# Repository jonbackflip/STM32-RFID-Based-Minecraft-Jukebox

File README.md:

# STM32-RFID-Based-Minecraft-Jukebox
An embedded music player based on the Minecraft Jukebox. Designed around an STM32F411CEU6, integrating RFID-based song selection, microSD storage, digital audio, user control via a rotary encoder with push-button, OLED display, and speaker/headphone output.

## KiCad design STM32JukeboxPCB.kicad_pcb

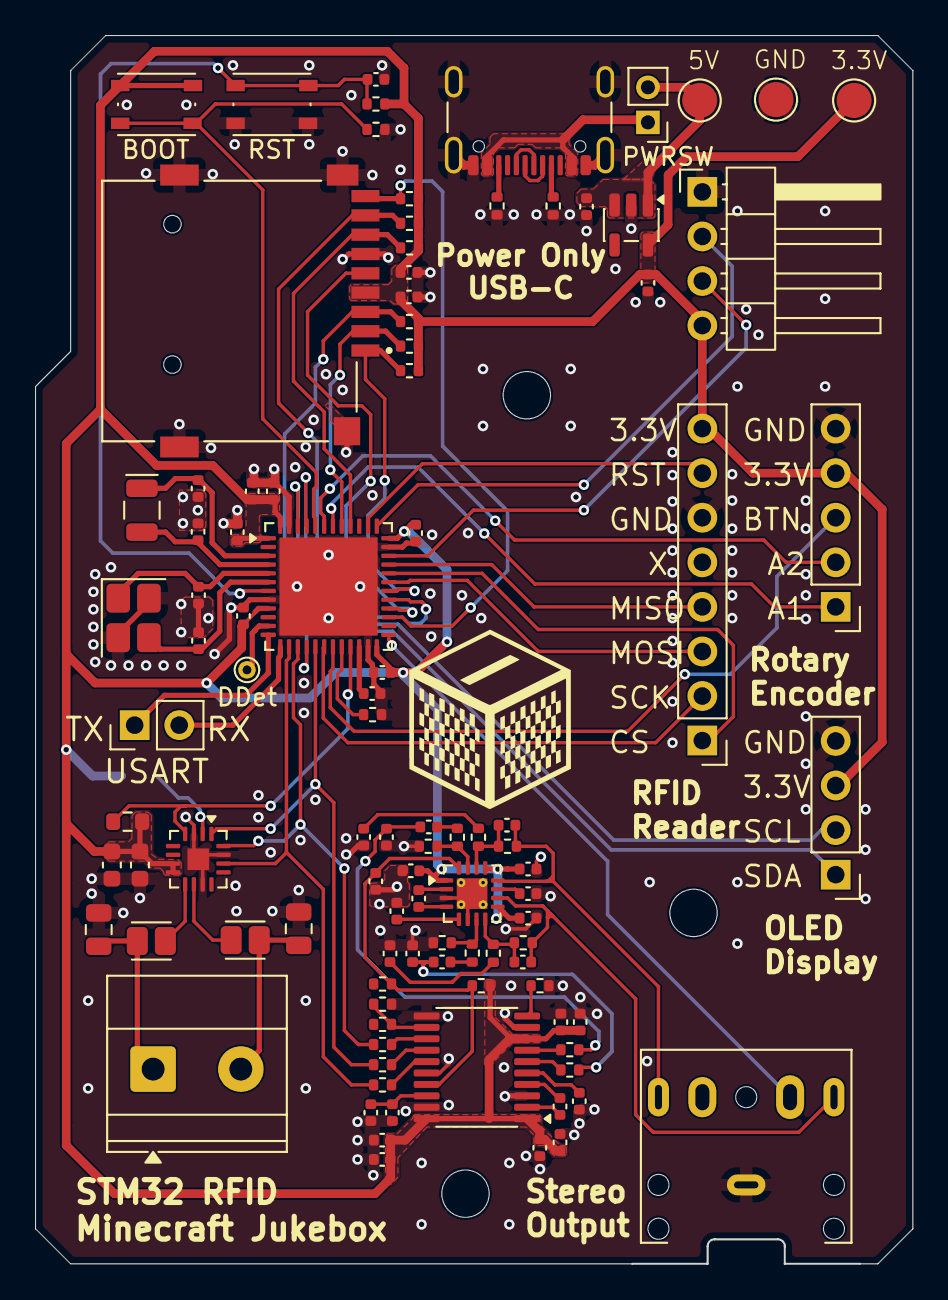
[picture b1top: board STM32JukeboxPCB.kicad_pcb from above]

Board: 4 copper layers, 50.0 x 70.0 mm, 104 parts (1 on the bottom side), 76 nets.

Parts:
C1, C15, C19, C20, C22, C23, C25, C26, C27, C28, C31, C41: 1uF; C_0402_1005Metric
C2, C3, C4, C5, C6, C7, C9, C10, C16, C29, C30, C40, C44: 0.1uF; C_0402_1005Metric
C8, C13, C14: 2.2uF; C_0402_1005Metric
C11, C12, C45: 10uF; C_0402_1005Metric
C17, C18: 2.2nF; C_0402_1005Metric
C21, C24: 6.8pF; C_0402_1005Metric
C32, C33: 0.22uF; C_0805_2012Metric
C34: 0.1uF; C_0603_1608Metric
C35: 1uF; C_0603_1608Metric
C36, C37: 8pF; C_0402_1005Metric
C38, C39: 1.5pF; C_0402_1005Metric
C42, C43: 4.7uF; C_0402_1005Metric
DDet: Conn_1x1; TestPoint_THTPad_D1.0mm_Drill0.5mm
FB1: FB1; L_Eaton_MCL2012V1
FB2: FB2; L_Eaton_MCL2012V1
H1, H2, H3: MountingHole; MountingHole_2.7mm_M2.5_DIN965
J1: MSD-1-A; CUI_MSD-1-A
J2: Screw_Terminal_1x2; TerminalBlock_Phoenix_MKDS-1,5-2_1x02_P5.00mm_Horizontal
J3: USB_C_Receptacle_USB2.0_16P; USB_C_Receptacle_GCT_USB4105-xx-A_16P_TopMnt_Horizontal
J4: AudioJack3_SwitchTR; Jack_3.5mm_CUI_SJ1-3525N_Horizontal
J5: Conn_01x08_Socket; PinHeader_1x08_P2.54mm_Vertical
J6: Conn_01x05; PinHeader_1x05_P2.54mm_Vertical
J7: Conn_01x04; PinHeader_1x04_P2.54mm_Vertical
J8: Conn_01x04_Pin; PinHeader_1x04_P2.54mm_Horizontal
J9: Conn_01x02_Pin; PinHeader_1x02_P2.54mm_Vertical
JP1: SolderJumper_3_Open; SolderJumper-3_P2.0mm_Open_TrianglePad1.0x1.5mm_NumberLabels
PWRSW: SW_SPST; PinHeader_1x02_P2.00mm_Vertical
R1, R2, R3, R4, R16, R19, R20, R21, R22, R23, R24: 10k; R_0402_1005Metric
R5, R6: 470; R_0402_1005Metric
R7, R8, R9, R10, R11, R12, R13, R14: 20k; R_0402_1005Metric
R15, R25, R26, R27, R28: 33; R_0402_1005Metric
R17, R18: 5.1k; R_0402_1005Metric
R29: 100k; R_0402_1005Metric
R30: 370k; R_0603_1608Metric
SW1, SW2: SW_Push; SW_Push_1P1T_NO_Vertical_Wuerth_434133025816
TP1: 5V_REF_PAD; TestPoint_Pad_D2.0mm
TP2: 3.3V_REF_PAD; TestPoint_Pad_D2.0mm
TP3: GND_REF_PAD; TestPoint_Pad_D2.0mm
U1: STM32F411CEUx; QFN-48-1EP_7x7mm_P0.5mm_EP5.6x5.6mm
U2: PCM5102A; TSSOP-20_4.4x6.5mm_P0.65mm
U3: MAX98357A; TQFN-16-1EP_3x3mm_P0.5mm_EP1.23x1.23mm
U4: TLV70233_SOT23-5; SOT-23-5
U5: HT97226; QFN-16-1EP_3x3mm_P0.5mm_EP1.75x1.75mm_ThermalVias
Y1: Crystal_GND23; Oscillator_SMD_SeikoEpson_SG210-4Pin_2.5x2.0mm_HandSoldering
Y2: Crystal; Crystal_SMD_MicroCrystal_CC7V-T1A-2Pin_3.2x1.5mm

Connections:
+3.3V: C1.1, C2.1, C3.1, C4.1, C5.1, C6.1, C9.1, C10.1, C11.1, C12.1, C26.1, C29.1, C31.1, C34.1, C35.2, C40.1, C41.2, C43.1, C44.1, C45.1, J1.4 (VDD), J5.8, J6.4, J7.3, J8.4, JP1.3 (B), R3.2, R16.1, R19.2, R20.2, R21.2, R22.2, R23.2, R24.2, R30.2, SW1.1, TP2.1 (1_1), U1.1 (VBAT), U1.9 (VDDA), U1.24 (VDD), U1.36 (VDD), U1.48 (VDD), U2.1 (CPVDD), U2.8 (AVDD), U2.20 (DVDD), U3.7 (VDD), U3.8 (VDD), U4.5 (OUT), U5.1 (PVDD), U5.9 (SVDD2), U5.13 (SVDD)
+5V: C42.1, PWRSW.2 (B), TP1.1 (1_1), U4.1 (IN), U4.3 (EN)
/Headphone DAC & Amplifier Sheet/AUDIO_L: C17.1, C19.1, R5.1
/Headphone DAC & Amplifier Sheet/AUDIO_R: C18.2, C22.1, R6.1
/Headphone DAC & Amplifier Sheet/BCK: R27.2, U1.15 (PA5), U3.16 (BCLK)
/Headphone DAC & Amplifier Sheet/CTRL: C25.1, R15.1, R16.2, U2.17 (XSMT), U5.16 (nSHDN)
/Headphone DAC & Amplifier Sheet/DIN: R26.2, U1.17 (PA7), U3.1 (DIN)
/Headphone DAC & Amplifier Sheet/HDPHN_JACK_DETECT: J4.TN, U1.25 (PB12)
/Headphone DAC & Amplifier Sheet/IN0+: R7.1, R8.2, U5.7 (INR+)
/Headphone DAC & Amplifier Sheet/IN0-: C21.1, R9.1, R10.2, U5.8 (INR-)
/Headphone DAC & Amplifier Sheet/IN1+: R11.1, R13.2, U5.15 (INL+)
/Headphone DAC & Amplifier Sheet/IN1-: C24.1, R12.1, R14.2, U5.14 (INL-)
/Headphone DAC & Amplifier Sheet/OUTL: C21.2, J4.T, R10.1, U5.10 (OUTR)
/Headphone DAC & Amplifier Sheet/OUTR: C24.2, J4.R, R14.1, U5.12 (OUTL)
/Headphone DAC & Amplifier Sheet/WS: R25.2, U1.14 (PA4), U3.14 (LRCLK)
/RFID MFRC522 Sheet/MISO: J5.4, U1.33 (PA12)
/RFID MFRC522 Sheet/MOSI: J5.3, U1.31 (PA10)
/RFID MFRC522 Sheet/RST: J5.7, U1.38 (PA15)
/RFID MFRC522 Sheet/SCK: J5.2, U1.18 (PB0)
/RFID MFRC522 Sheet/SDA / CS: J5.1, U1.32 (PA11)
/Rotary Encoder Sheet/A1: J6.1, U1.42 (PB6)
/Rotary Encoder Sheet/A2: J6.2, U1.43 (PB7)
/Rotary Encoder Sheet/BTN: J6.3, U1.19 (PB1)
/SD Card Sheet/SDIO_CK: J1.5 (CLK), U1.28 (PB15)
/SD Card Sheet/SDIO_CMD: J1.3 (CMD), R19.1, U1.16 (PA6)
/SD Card Sheet/SDIO_D0: J1.7 (DAT0), R20.1, U1.40 (PB4)
/SD Card Sheet/SDIO_D1: J1.8 (DAT1), R21.1, U1.29 (PA8)
/SD Card Sheet/SDIO_D2: J1.1 (DAT2), R22.1, U1.30 (PA9)
/SD Card Sheet/SDIO_D3: J1.2 (CD/DAT3), R23.1, U1.41 (PB5)
/SD Card Sheet/SD_DETECT: J1.CD, R24.1, U1.27 (PB14)
/SSD1306 OLED Sheet/SCL: J7.2, U1.45 (PB8)
/SSD1306 OLED Sheet/SDA: J7.1, U1.46 (PB9)
/STM32F411 Sheet/BOOT0: R1.2, SW1.2, U1.44 (BOOT0)
/STM32F411 Sheet/Insert_Disc_Detect: DDet.1 (Pin_1_1), U1.11 (PA1)
/STM32F411 Sheet/LSE_OSC_IN: C38.1, U1.3 (PC14), Y2.1
/STM32F411 Sheet/LSE_OSC_OUT: C39.1, U1.4 (PC15), Y2.2
/STM32F411 Sheet/NRST: C7.1, R3.1, SW2.1, U1.7 (NRST)
/STM32F411 Sheet/PB2: R2.2, U1.20 (PB2)
/STM32F411 Sheet/RCC_OSC_IN: C36.1, U1.5 (PH0), Y1.1
/STM32F411 Sheet/RCC_OSC_OUT: C37.1, U1.6 (PH1), Y1.3
/STM32F411 Sheet/SPEAKER_ENABLE: R30.1, U1.21 (PB10), U3.4 (~SD_MODE)
/STM32F411 Sheet/SYS_JTCK-SWCLK: J8.2, U1.37 (PA14)
/STM32F411 Sheet/SYS_JTMS-SWDIO: J8.3, U1.34 (PA13)
/STM32F411 Sheet/USART2_RX: J9.2, U1.13 (PA3)
/STM32F411 Sheet/USART2_TX: J9.1, U1.12 (PA2)
/STM32F411 Sheet/USB_5V: J3.A4 (VBUS), J3.A9 (VBUS), J3.B4 (VBUS), J3.B9 (VBUS), PWRSW.1 (A)
/Speaker DAC & Amplifier Sheet/GAIN: JP1.2 (C), U3.2 (GAIN_SLOT)
/Speaker DAC & Amplifier Sheet/MAX_OUTN: FB2.1, U3.10 (OUTN)
/Speaker DAC & Amplifier Sheet/MAX_OUTP: FB1.1, U3.9 (OUTP)
/Speaker DAC & Amplifier Sheet/SPEAKER_OUTN: C33.1, FB2.2, J2.2
/Speaker DAC & Amplifier Sheet/SPEAKER_OUTP: C32.2, FB1.2, J2.1
D+: J3.A6 (D+), J3.B6 (D+)
D-: J3.A7 (D-), J3.B7 (D-)
GND: C1.2, C2.2, C3.2, C4.2, C5.2, C6.2, C7.2, C8.2, C9.2, C10.2, C11.2, C12.2, C14.2, C15.2, C16.2, C17.2, C18.1, C20.1, C23.1, C25.2, C26.2, C28.2, C29.2, C30.2, C31.2, C32.1, C33.2, C34.2, C35.1, C36.2, C37.2, C38.2, C39.2, C40.2, C41.1, C42.2, C43.2, C44.2, C45.2, J1.6 (VSS), J1.G1 (COVER_GND), J1.G2 (COVER_GND__1), J1.G3 (COVER_GND__2), J1.G4 (COVER_GND__3), J3.A1 (GND), J3.A12 (GND), J3.B1 (GND), J3.B12 (GND), J3.S1 (SHIELD), J4.S, J5.6, J6.5, J7.4, J8.1, JP1.1 (A), R1.1, R2.1, R4.1, R8.1, R13.1, R17.1, R18.1, R29.2, SW2.2, TP3.1 (1_1), U1.8 (VSSA), U1.23 (VSS), U1.35 (VSS), U1.47 (VSS), U1.49 (VSS), U2.3 (CPGND), U2.9 (AGND), U2.11 (FLT), U2.16 (FMT), U2.19 (DGND), U3.3 (GND), U3.11 (GND), U3.15 (GND), U3.17 (PAD), U4.2 (GND), U5.3 (PGND), U5.6 (SGND), U5.17 (EP), Y1.2 (G), Y1.4 (G)
unnamed: C19.2, R7.2
unnamed: C20.2, R9.2
unnamed: C22.2, R11.2
unnamed: C23.2, R12.2
unnamed: J3.A5 (CC1), R17.2
unnamed: J3.B5 (CC2), R18.2
unnamed: C8.1, U1.22 (VCAP1)
unnamed: R27.1, U2.13 (BCK)
unnamed: C13.2, U2.4 (CAPM)
unnamed: C13.1, U2.2 (CAPP)
unnamed: R4.2, U2.10 (DEMP)
unnamed: R26.1, U2.14 (DIN)
unnamed: C15.1, C16.1, U2.18 (LDOO)
unnamed: R25.1, U2.15 (LRCK)
unnamed: R5.2, U2.6 (OUTL)
unnamed: R6.2, U2.7 (OUTR)
unnamed: R28.1, R29.1, U2.12 (SCK)
unnamed: C14.1, U2.5 (VNEG)
unnamed: C30.1, U5.11 (BIAS)
unnamed: C27.2, U5.4 (C1N)
unnamed: C27.1, U5.2 (C1P)
unnamed: C28.1, U5.5 (PVSS)

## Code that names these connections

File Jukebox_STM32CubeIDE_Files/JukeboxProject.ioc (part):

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Mcu.Name=STM32F411C(C-E)Ux
Mcu.Package=UFQFPN48
Mcu.UserName=STM32F411CEUx
PA1.GPIOParameters=GPIO_PuPd,GPIO_Label,GPIO_ModeDefaultEXTI
PA1.GPIO_Label=Disc_Insertion_BTN
PA1.GPIO_ModeDefaultEXTI=GPIO_MODE_IT_FALLING
PA1.GPIO_PuPd=GPIO_PULLUP
PA1.Signal=GPXTI1
PA10.Mode=Full_Duplex_Master
PA10.Signal=SPI5_MOSI
PA11.GPIOParameters=GPIO_Label
PA11.GPIO_Label=CS
PA11.Signal=GPIO_Output
PA12.Mode=Full_Duplex_Master
PA12.Signal=SPI5_MISO
PA13.Mode=Serial_Wire
PA13.Signal=SYS_JTMS-SWDIO
PA14.Mode=Serial_Wire
PA14.Signal=SYS_JTCK-SWCLK
PA15.GPIOParameters=GPIO_Label
PA15.GPIO_Label=RESET
PA15.Signal=GPIO_Output
PA2.Mode=Asynchronous
PA2.Signal=USART2_TX
PA3.Mode=Asynchronous
PA3.Signal=USART2_RX
PA4.Mode=Half_Duplex_Master
PA4.Signal=I2S1_WS
PA5.Mode=Half_Duplex_Master
PA5.Signal=I2S1_CK
PA6.GPIOParameters=GPIO_PuPd
PA6.GPIO_PuPd=GPIO_PULLUP
PA6.Mode=SD_4_bits_Wide_bus
PA6.Signal=SDIO_CMD
PA7.Mode=Half_Duplex_Master
PA7.Signal=I2S1_SD
PA8.GPIOParameters=GPIO_PuPd
PA8.GPIO_PuPd=GPIO_PULLUP
PA8.Mode=SD_4_bits_Wide_bus
PA8.Signal=SDIO_D1
PA9.GPIOParameters=GPIO_PuPd
PA9.GPIO_PuPd=GPIO_PULLUP
PA9.Mode=SD_4_bits_Wide_bus
PA9.Signal=SDIO_D2
PB0.Mode=Full_Duplex_Master
PB0.Signal=SPI5_SCK
PB1.GPIOParameters=GPIO_PuPd,GPIO_Label
PB1.GPIO_Label=PAUSE_BTN
PB1.GPIO_PuPd=GPIO_PULLUP
PB1.Signal=GPIO_Input
PB10.GPIOParameters=GPIO_PuPd,GPIO_Label
PB10.GPIO_Label=SPEAKER_ENABLE
PB10.GPIO_PuPd=GPIO_PULLUP
PB10.Signal=GPIO_Output
PB12.GPIOParameters=GPIO_Label
PB12.GPIO_Label=HEADPHONE_JACK_DETECT
PB12.Signal=GPIO_Input
PB14.GPIOParameters=GPIO_Label
PB14.GPIO_Label=SD_DETECT
PB14.Signal=GPIO_Input
PB15.Mode=SD_4_bits_Wide_bus
PB15.Signal=SDIO_CK
PB4.GPIOParameters=GPIO_PuPd
PB4.GPIO_PuPd=GPIO_PULLUP
PB4.Mode=SD_4_bits_Wide_bus
PB4.Signal=SDIO_D0
PB5.GPIOParameters=GPIO_PuPd
PB5.GPIO_PuPd=GPIO_PULLUP
PB5.Mode=SD_4_bits_Wide_bus
PB5.Signal=SDIO_D3
PB6.Signal=S_TIM4_CH1
PB7.Signal=S_TIM4_CH2
PB8.Mode=I2C
PB8.Signal=I2C1_SCL
PB9.Mode=I2C
PB9.Signal=I2C1_SDA
PC13-ANTI_TAMP.Signal=GPIO_Output
PH0\ -\ OSC_IN.Mode=HSE-External-Oscillator
PH0\ -\ OSC_IN.Signal=RCC_OSC_IN
PH1\ -\ OSC_OUT.Mode=HSE-External-Oscillator
PH1\ -\ OSC_OUT.Signal=RCC_OSC_OUT
RCC.HSE_VALUE=8000000
RCC.SYSCLKFreq_VALUE=100000000
RCC.SYSCLKSource=RCC_SYSCLKSOURCE_PLLCLK
board=custom
